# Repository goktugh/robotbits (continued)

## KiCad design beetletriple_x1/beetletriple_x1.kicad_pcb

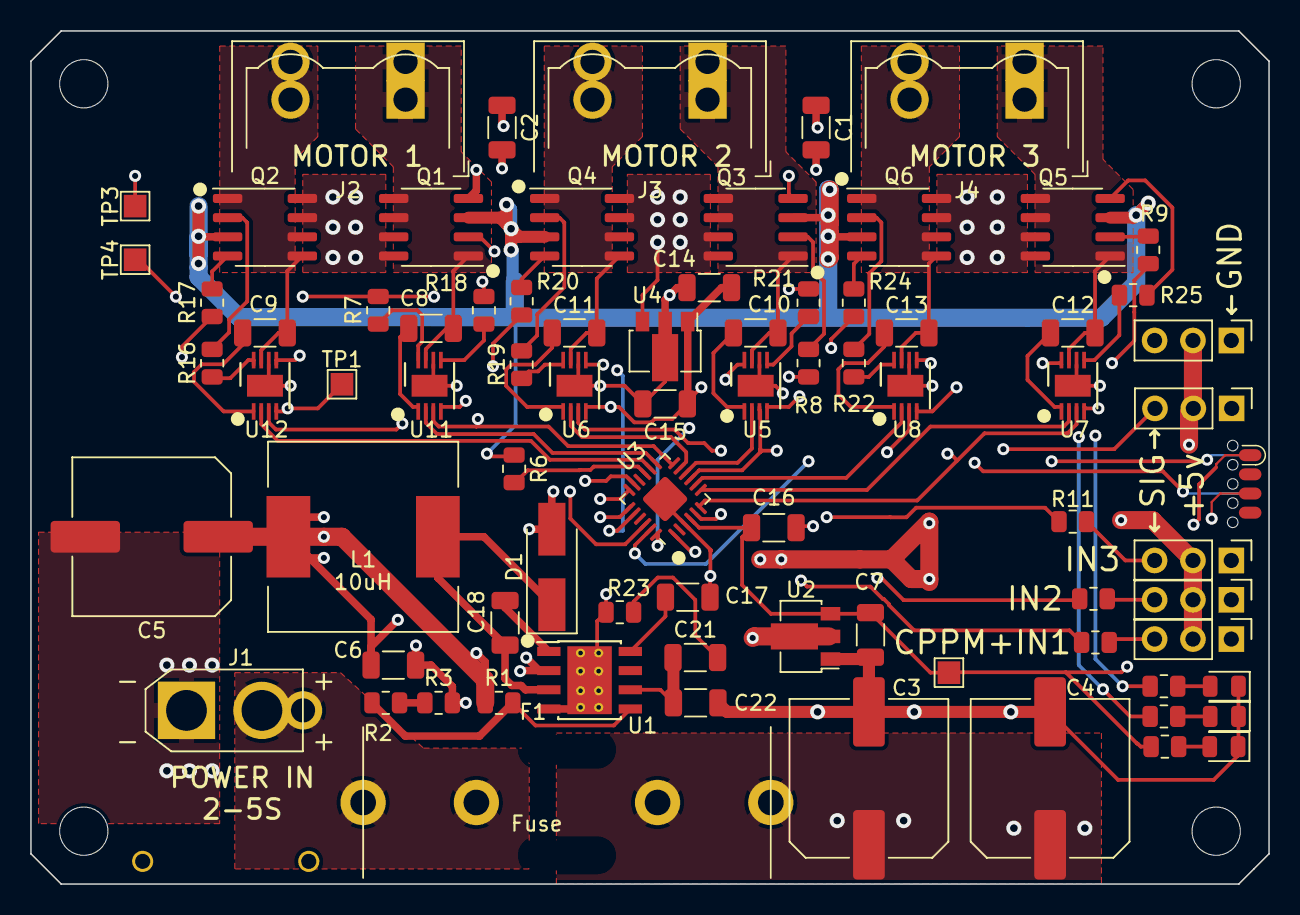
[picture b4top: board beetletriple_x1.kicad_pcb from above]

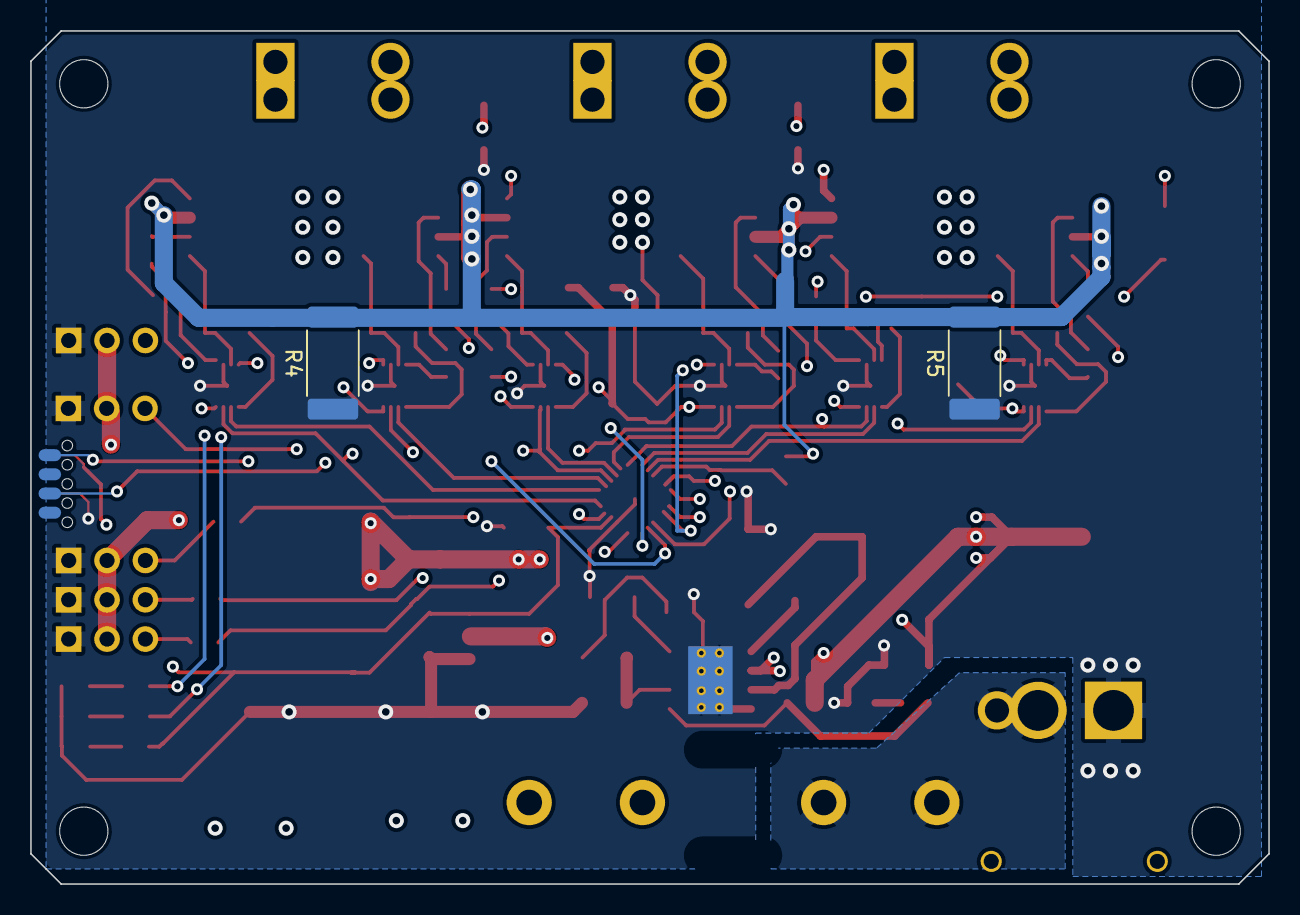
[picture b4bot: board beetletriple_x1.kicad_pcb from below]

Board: 4 copper layers, 82.0 x 56.5 mm, 81 parts (2 on the bottom side), 75 nets.

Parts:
C1, C2, C6, C7, C15: 10uF 50V; C_1206_3216Metric
C3, C4, C5: 220uF; C_Elec_10x10.2
C8, C9, C10, C11, C12, C13, C14, C16: 2.2uF 50V; C_1206_3216Metric
C17: 10nF; C_1206_3216Metric
C18: 0.1uF; C_1206_3216Metric
C21, C22: DNP; C_1206_3216Metric
D1: B340A-13-F; D_SMA_Handsoldering
D8, D9: Green; LED_0805_2012Metric
D10: Orange; LED_0805_2012Metric
F1: 20mmx5 fuse holder; fuseholder_bs1363
J1: Power IN; beetlepower
J2, J3, J4: motor_out; TerminalBlock_motor
J5: input_c1; PinHeader_1x03_P2.54mm_Vertical
J6: input_c2; PinHeader_1x03_P2.54mm_Vertical
J7: input_c3; PinHeader_1x03_P2.54mm_Vertical
J8: output_c4; PinHeader_1x03_P2.54mm_Vertical
J9: output_c5; PinHeader_1x03_P2.54mm_Vertical
J10: soicbite programming connector; SOIC_clipProgSmall
L1: 10uH; L_12x12mm_H4.5mm
Q1, Q2, Q3, Q4, Q5, Q6: IRF8313PBF; SOIC-8_3.9x4.9mm_P1.27mm
R1: 10k; R_0805_2012Metric
R2, R6, R10, R11, R12, R13, R14, R15: 1.5k; R_0805_2012Metric
R3: 100R; R_0805_2012Metric
R4, R5: 0.01R shunt; R_2512_6332Metric_Pad1.40x3.35mm_HandSolder
R7, R8, R9, R16, R17, R18, R19, R20, R21, R22, R24, R25: 10R; R_0805_2012Metric
R23: DNP; R_0805_2012Metric
TP1, TP2, TP3, TP4: TestPoint; TestPoint_Pad_1.5x1.5mm
U1: TPS54331DR; TI_SO-PowerPAD-8_ThermalVias
U2: HT7550-1; SOT-89-3
U3: ATtiny1617-M; qfn24-hand1
U4: 78L12G-AB3-R; SOT-89-3
U5, U6, U7, U8, U11, U12: NCP81155MNTXG; DFN-8-3x3mm_hand1

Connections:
+12V: C14.1, C15.1, TP1.1, U4.1 (OUT), U5.4 (VCC), U6.4 (VCC), U7.4 (VCC), U8.4 (VCC), U11.4 (VCC), U12.4 (VCC)
/MCU/BLINKY1: R14.2, U3.22 (PC5)
/MCU/BLINKY2: R15.2, U3.17 (PC0)
/MCU/RXIN1: R10.2, U3.1 (PA2)
/MCU/RXIN2: R12.2, U3.19 (PC2)
/MCU/RXIN3: R11.2, U3.5 (PA4)
/MCU/SERVO1: J8.3, U3.20 (PC3)
/MCU/SERVO2: J9.3, U3.18 (PC1)
/MCU/TXDEBUG: J10.8, U3.24 (PA1)
/MCU/UPDI: J10.6, U3.23 (~RESET~/PA0)
/Power/COMP: C21.1, C22.1, U1.6 (COMP)
/Power/REG_BOOT: C18.1, U1.1 (BOOT)
/Power/REG_PH: C18.2, D1.1 (K), L1.1, U1.3 (PH)
/Power/REG_SENSE: R1.2, R2.1, U1.5 (VSENSE)
/Power/REG_SOFTSTART: C17.1, U1.8 (SS)
/driver1/GATEH1: Q1.2 (G), R7.2, TP4.1
/driver1/GATEH2: Q2.2 (G), R16.2
/driver1/GATEL1: Q1.4 (G), R18.2, TP3.1
/driver1/GATEL2: Q2.4 (G), R17.2
/driver1/MOTORH1: R7.1, U11.8 (DRVH)
/driver1/MOTORH2: R16.1, U12.8 (DRVH)
/driver1/MOTORL1: R18.1, U11.5 (DRVL)
/driver1/MOTORL2: R17.1, U12.5 (DRVL)
/driver1/MOTORS1: C8.2, J2.1, Q1.1 (S), Q1.5 (D), Q1.6 (D), U11.7 (SW)
/driver1/MOTORS2: C9.2, J2.2, Q2.1 (S), Q2.5 (D), Q2.6 (D), U12.7 (SW)
/driver2/GATEH1: Q3.2 (G), R8.2
/driver2/GATEH2: Q4.2 (G), R19.2
/driver2/GATEL1: Q3.4 (G), R21.2
/driver2/GATEL2: Q4.4 (G), R20.2
/driver2/MOTORH1: R8.1, U5.8 (DRVH)
/driver2/MOTORH2: R19.1, U6.8 (DRVH)
/driver2/MOTORL1: R21.1, U5.5 (DRVL)
/driver2/MOTORL2: R20.1, U6.5 (DRVL)
/driver2/MOTORS1: C10.2, J3.1, Q3.1 (S), Q3.5 (D), Q3.6 (D), U5.7 (SW)
/driver2/MOTORS2: C11.2, J3.2, Q4.1 (S), Q4.5 (D), Q4.6 (D), U6.7 (SW)
/driver3/GATEH1: Q5.2 (G), R9.2
/driver3/GATEH2: Q6.2 (G), R22.2
/driver3/GATEL1: Q5.4 (G), R25.2
/driver3/GATEL2: Q6.4 (G), R24.2
/driver3/MOTORH1: R9.1, U7.8 (DRVH)
/driver3/MOTORH2: R22.1, U8.8 (DRVH)
/driver3/MOTORL1: R25.1, U7.5 (DRVL)
/driver3/MOTORL2: R24.1, U8.5 (DRVL)
/driver3/MOTORS1: C12.2, J4.1, Q5.1 (S), Q5.5 (D), Q5.6 (D), U7.7 (SW)
/driver3/MOTORS2: C13.2, J4.2, Q6.1 (S), Q6.5 (D), Q6.6 (D), U8.7 (SW)
CURRENTSENSE: R6.2, U3.15 (PB1)
GND: C1.2, C2.2, C3.2, C4.2, C5.2, C6.2, C7.2, C14.2, C15.2, C16.2, C17.2, C22.2, D1.2 (A), D8.1 (K), D9.1 (K), D10.1 (K), J1.1, J5.1, J6.1, J7.1, J8.1, J9.1, J10.3, R3.2, R4.1, R5.1, R23.2, U1.4 (GND), U1.9 (ETPAD), U2.1 (GND), U3.3 (GND), U3.25 (GND), U4.2 (GND), U5.6 (GND), U5.9 (FLAG), U6.6 (GND), U6.9 (FLAG), U7.6 (GND), U7.9 (FLAG), U8.6 (GND), U8.9 (FLAG), U11.6 (GND), U11.9 (FLAG), U12.6 (GND), U12.9 (FLAG)
GNDSHUNT: Q1.3 (S), Q2.3 (S), Q3.3 (S), Q4.3 (S), Q5.3 (S), Q6.3 (S), R4.2, R5.2, R6.1
MOTOR1D1: U3.13 (PB3), U11.2 (PWM)
MOTOR1D2: U3.14 (PB2), U12.2 (PWM)
MOTOR1EN: U3.12 (PB4), U11.3 (EN), U12.3 (EN)
MOTOR2D1: U3.10 (PB6), U5.2 (PWM)
MOTOR2D2: U3.11 (PB5), U6.2 (PWM)
MOTOR2EN: U3.9 (PB7), U5.3 (EN), U6.3 (EN)
MOTOR3D1: U3.7 (PA6), U7.2 (PWM)
MOTOR3D2: U3.8 (PA7), U8.2 (PWM)
MOTOR3EN: U3.6 (PA5), U7.3 (EN), U8.3 (EN)
unnamed: C8.1, U11.1 (BST)
unnamed: C9.1, U12.1 (BST)
unnamed: C10.1, U5.1 (BST)
unnamed: C11.1, U6.1 (BST)
unnamed: C12.1, U7.1 (BST)
unnamed: C13.1, U8.1 (BST)
unnamed: C21.2, R23.1
unnamed: D8.2 (A), R13.1
unnamed: D9.2 (A), R14.1
unnamed: D10.2 (A), R15.1
unnamed: J5.3, R10.1
unnamed: J6.3, R12.1
unnamed: J7.3, R11.1
unnamed: R2.2, R3.1
VBAT: C1.1, C2.1, C3.1, C4.1, F1.2, Q1.7 (D), Q1.8 (D), Q2.7 (D), Q2.8 (D), Q3.7 (D), Q3.8 (D), Q4.7 (D), Q4.8 (D), Q5.7 (D), Q5.8 (D), Q6.7 (D), Q6.8 (D), U1.2 (VIN), U4.3 (IN)
VBAT_IN_1: F1.1, J1.2
VBEC: C5.1, C6.1, J5.2, J6.2, J7.2, J8.2, J9.2, L1.2, R1.1, U2.2 (VIN)
VLOGIC: C7.1, C16.1, J10.1, R13.2, TP2.1, U2.3 (VOUT), U3.4 (VCC)

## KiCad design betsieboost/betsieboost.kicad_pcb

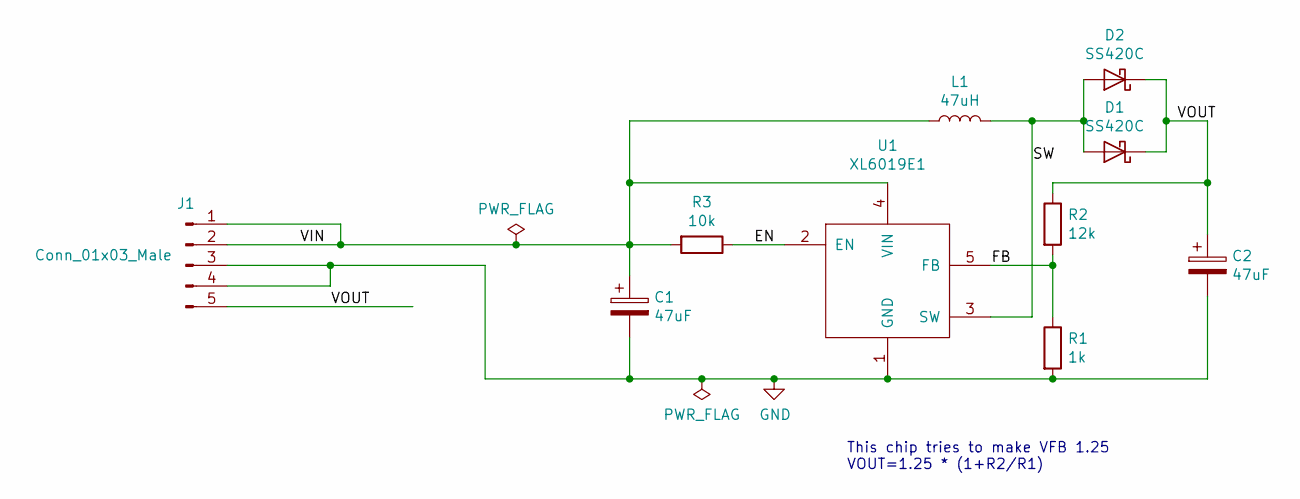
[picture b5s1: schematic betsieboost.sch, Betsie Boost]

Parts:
C1, C2: 47uF; CP_EIA-7343-30_AVX-N
D1, D2: SS420C; D_2816_7142Metric
J1: Conn_01x03_Male; PinHeader_1x05_P2.54mm_BIG1
L1: 47uH; L_10.4x10.4_H4.8
R1: 1k; R_0805_2012Metric_Pad1.15x1.40mm_HandSolder
R2: 12k; R_0805_2012Metric_Pad1.15x1.40mm_HandSolder
R3: 10k; R_0805_2012Metric_Pad1.15x1.40mm_HandSolder
U1: XL6019E1; TO-263-5_TabPin3

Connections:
/EN: R3.1, U1.2 (EN)
/FB: R1.1, R2.2, U1.5 (FB)
/SW: D1.2 (A), D2.2 (A), L1.2, U1.3 (SW)
/VIN: C1.1, J1.1, J1.2, L1.1, R3.2, U1.4 (VIN)
/VOUT: C2.1, D1.1 (K), D2.1 (K), J1.5, R2.1; also elsewhere on the board
GND: C1.2, C2.2, J1.3, J1.4, R1.2, U1.1 (GND); also elsewhere on the board

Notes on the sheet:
This chip tries to make VFB 1.25 VOUT=1.25 * (1+R2/R1)

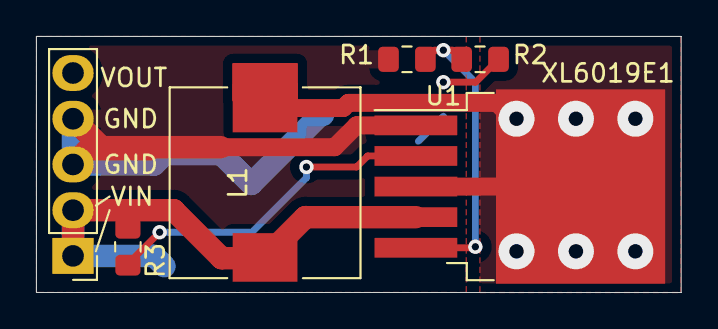
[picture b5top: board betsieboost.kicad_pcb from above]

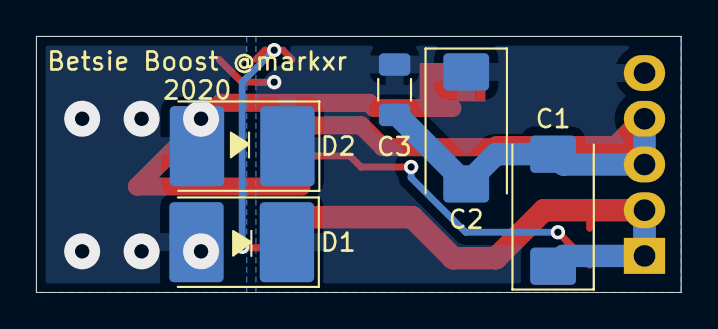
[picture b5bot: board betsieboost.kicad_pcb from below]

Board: 2 copper layers, 35.8 x 14.2 mm, 11 parts (5 on the bottom side), 6 nets.

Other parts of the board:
C3: 10uF; C_1206_3216Metric

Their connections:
/VOUT: C3.1; also elsewhere on the board
GND: C3.2; also elsewhere on the board

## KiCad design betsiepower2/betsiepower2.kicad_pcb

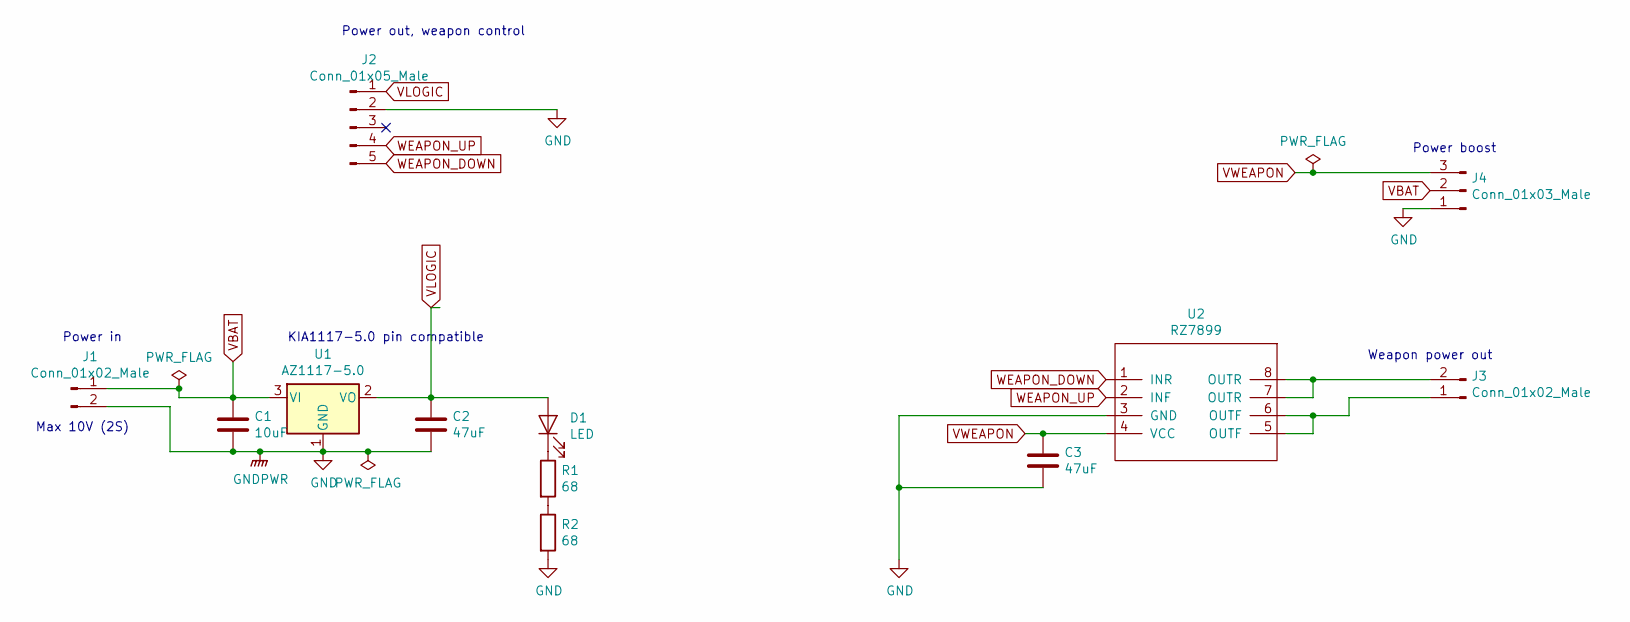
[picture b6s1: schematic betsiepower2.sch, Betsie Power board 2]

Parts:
C1: 10uF; C_0805_HandSoldering
C2, C3: 47uF; C_1206_HandSoldering
D1: LED; LED_0805
J1, J3: Conn_01x02_Male; Pin_Header_Straight_1x02_Pitch2.54mm
J2: Conn_01x05_Male; Pin_Header_Straight_1x05_Pitch2.54mm
J4: Conn_01x03_Male; Pin_Header_Straight_1x03_Pitch2.54mm
R1, R2: 68; R_0805_HandSoldering
U1: AZ1117-5.0; SOT-223
U2: RZ7899; SOIC-8_3.9x4.9mm_Pitch1.27mm

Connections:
GND: C1.2, C2.2, C3.2, J1.2, J2.2, J4.1, R2.2, U1.1 (GND), U2.3 (GND)
unnamed: D1.1 (K), R1.1
unnamed: J3.1, U2.5 (OUTF), U2.6 (OUTF)
unnamed: J3.2, U2.7 (OUTR), U2.8 (OUTR)
unnamed: R1.2, R2.1
VBAT: C1.1, J1.1, J4.2, U1.3 (VI)
VLOGIC: C2.1, D1.2 (A), J2.1, U1.2 (VO)
VWEAPON: C3.1, J4.3, U2.4 (VCC)
WEAPON_DOWN: J2.5, U2.1 (INR)
WEAPON_UP: J2.4, U2.2 (INF)

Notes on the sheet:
Power out, weapon control
Power in
KIA1117-5.0 pin compatible
Max 10V (2S)
Weapon power out
Power boost

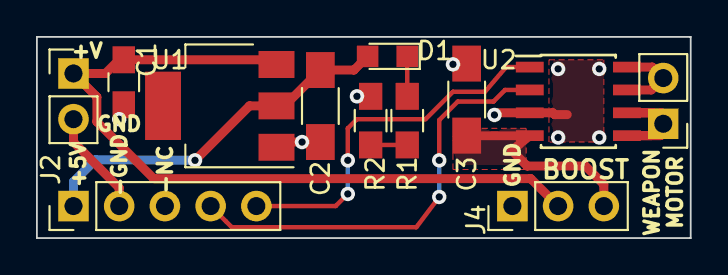
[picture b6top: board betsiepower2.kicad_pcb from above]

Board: 2 copper layers, 36.3 x 11.2 mm, 12 parts (0 on the bottom side), 10 nets.

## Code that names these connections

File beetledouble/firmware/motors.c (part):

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static uint16_t overflow_count;

/*
 * PB0 - MOTOR_ENABLE_1 - Active high enables the gates on M1
    Also connected to LED.
PA4 - MOTORF_1 - drives side 1 of M1 high
PA5 - MOTORR_1 - drives side 2 of M2 high



PB1 - MOTOR_ENABLE_2 - Active high enables the gates on M2
PA6 - MOTORF_2
PA7 - MOTORR_2
*/

// Enable pins:

#define PORT_MOTOR_ENABLE_1 PORTB
#define PIN_MOTOR_ENABLE_1 2

#define PORT_MOTOR_ENABLE_2 PORTB
#define PIN_MOTOR_ENABLE_2 1

// Gate drive pins

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    // set all the half bridges to low
	PORT_MOTOR.OUTCLR = BITMAP_ALL_MOTORS;
    // Enable it all
	PORT_MOTOR_ENABLE_1.OUTSET = (1<< PIN_MOTOR_ENABLE_1);
	PORT_MOTOR_ENABLE_2.OUTSET = (1<< PIN_MOTOR_ENABLE_2);
}

void motors_early_init()
{
    // SO that the outputs are not floating, or
    // If we had a bootloader or updi or something which left the pins
    // in a weird state,
    // Turn everything off as soon as possible. 
	// Make enable pins outputs.
	PORT_MOTOR_ENABLE_1.DIRSET = (1<< PIN_MOTOR_ENABLE_1); 
	PORT_MOTOR_ENABLE_2.DIRSET = (1<< PIN_MOTOR_ENABLE_2);
	
	// Make the gate drive pins outputs.
	PORT_MOTOR.DIRSET = BITMAP_ALL_MOTORS;
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	
	if (index==0) {
		port_enable = &PORT_MOTOR_ENABLE_1;
		pin_enable = PIN_MOTOR_ENABLE_1;
		pin_forward = PIN_MOTOR1F;
		pin_reverse = PIN_MOTOR1R;
	} else {
		port_enable = &PORT_MOTOR_ENABLE_2;
		pin_enable = PIN_MOTOR_ENABLE_2;
		pin_forward = PIN_MOTOR2F;
		pin_reverse = PIN_MOTOR2R;
	}
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 */
void motors_overcurrent_off()
{
	PORT_MOTOR_ENABLE_1.OUTCLR = (1<< PIN_MOTOR_ENABLE_1);
	PORT_MOTOR_ENABLE_2.OUTCLR = (1<< PIN_MOTOR_ENABLE_2);
	PORT_MOTOR.OUTCLR = BITMAP_ALL_MOTORS;
}

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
